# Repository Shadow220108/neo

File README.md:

<h1 align="center">
<br>

<br>
Neo
<br>
</h1>

<h3 align="center">

A wireless 75% keyboard 

</h3>

<div align="center">
  
</div>

Neo is a 75% mechanical keyboard built around the Nordic nRF52840. It works over Bluetooth and over USB-C, runs on a LiPo battery that charges from the same USB-C port, and it has hotswap switches so you can change the switches without soldering anything. The PCB is a 4 layer board designed in KiCad and the case is designed in Fusion 360.

## Features

- 84 keys in a 75% ANSI layout, so you still get the F row and arrow keys
- Bluetooth 5 and USB-C from one chip (nRF52840), works with ZMK
- Kailh hotswap sockets for MX style switches
- Single cell LiPo with an MCP73831 charger, it charges while you use it
- Power switch that cuts the regulator but still lets the battery charge
- XC6220 regulator with only 8uA idle current so the battery lasts long
- Battery voltage reading so you can see the battery percentage
- 2.4GHz chip antenna with a keepout area on all 4 layers
- SWD header for flashing the bootloader
- 3 part case (bottom, plate, top frame) with a typing angle

## PCB

| Switches | MCU and antenna |
| --- | --- |
|  |  |

The board is 304.8 x 144.3 mm with 4 layers. Top and bottom have the signals and a ground fill, inner 1 is a solid ground plane and inner 2 has some power traces. The matrix is 6 rows and 16 columns with a 1N4148W diode on every key. There are 512 vias on it which is kinda crazy lol.

The USB-C has 5.1k resistors on CC1 and CC2 so C to C chargers work, a 500mA fuse and a USBLC6 ESD chip. When USB is plugged in the keyboard runs from USB and charges the battery, and when you unplug it an AO3401A switches over to the battery.

| USB-C | Charger |
| --- | --- |
|  |  |

## Case

The case has 3 parts, a bottom tray with a tilt, a switch plate and a red top frame with some vent lines on it just for the looks. The PCB screws in with 6 M2 holes. Each part is about 314 x 159 mm, so you need a big printer bed for it or you have to split the parts.

| Bottom | Plate |
| --- | --- |
|  |  |

## Renders

| Red | Orange |
| --- | --- |
|  |  |

## BOM

|Component   |Description                                                               |Qty|Unit price ($)|Total ($)|Source       |
|------------|--------------------------------------------------------------------------|---|--------------|---------|-------------|
|PCBA        |JLCPCB 4 layer PCB, assembled                                             |1  |73.40         |73.40    |JLCPCB       |
|Switches    |Gateron G Pro 3.0, pack of 90                                             |1  |18.45         |18.45    |Kinetic Labs |
|Keycaps     |Keychron double shot PBT Cherry profile full set (218 keys, fits 75% ANSI)|1  |39.99         |39.99    |Keychron     |
|Stabilizers |Durock V3 screw-in set (4x 2u, 1x 6.25u)                                  |1  |13.99         |13.99    |Divinikey    |
|LiPo battery|3.7V 2000mAh, JST-PH                                                      |1  |12.50         |12.50    |Adafruit 2011|
|Total       |                                                                          |   |              |158.33   |             |

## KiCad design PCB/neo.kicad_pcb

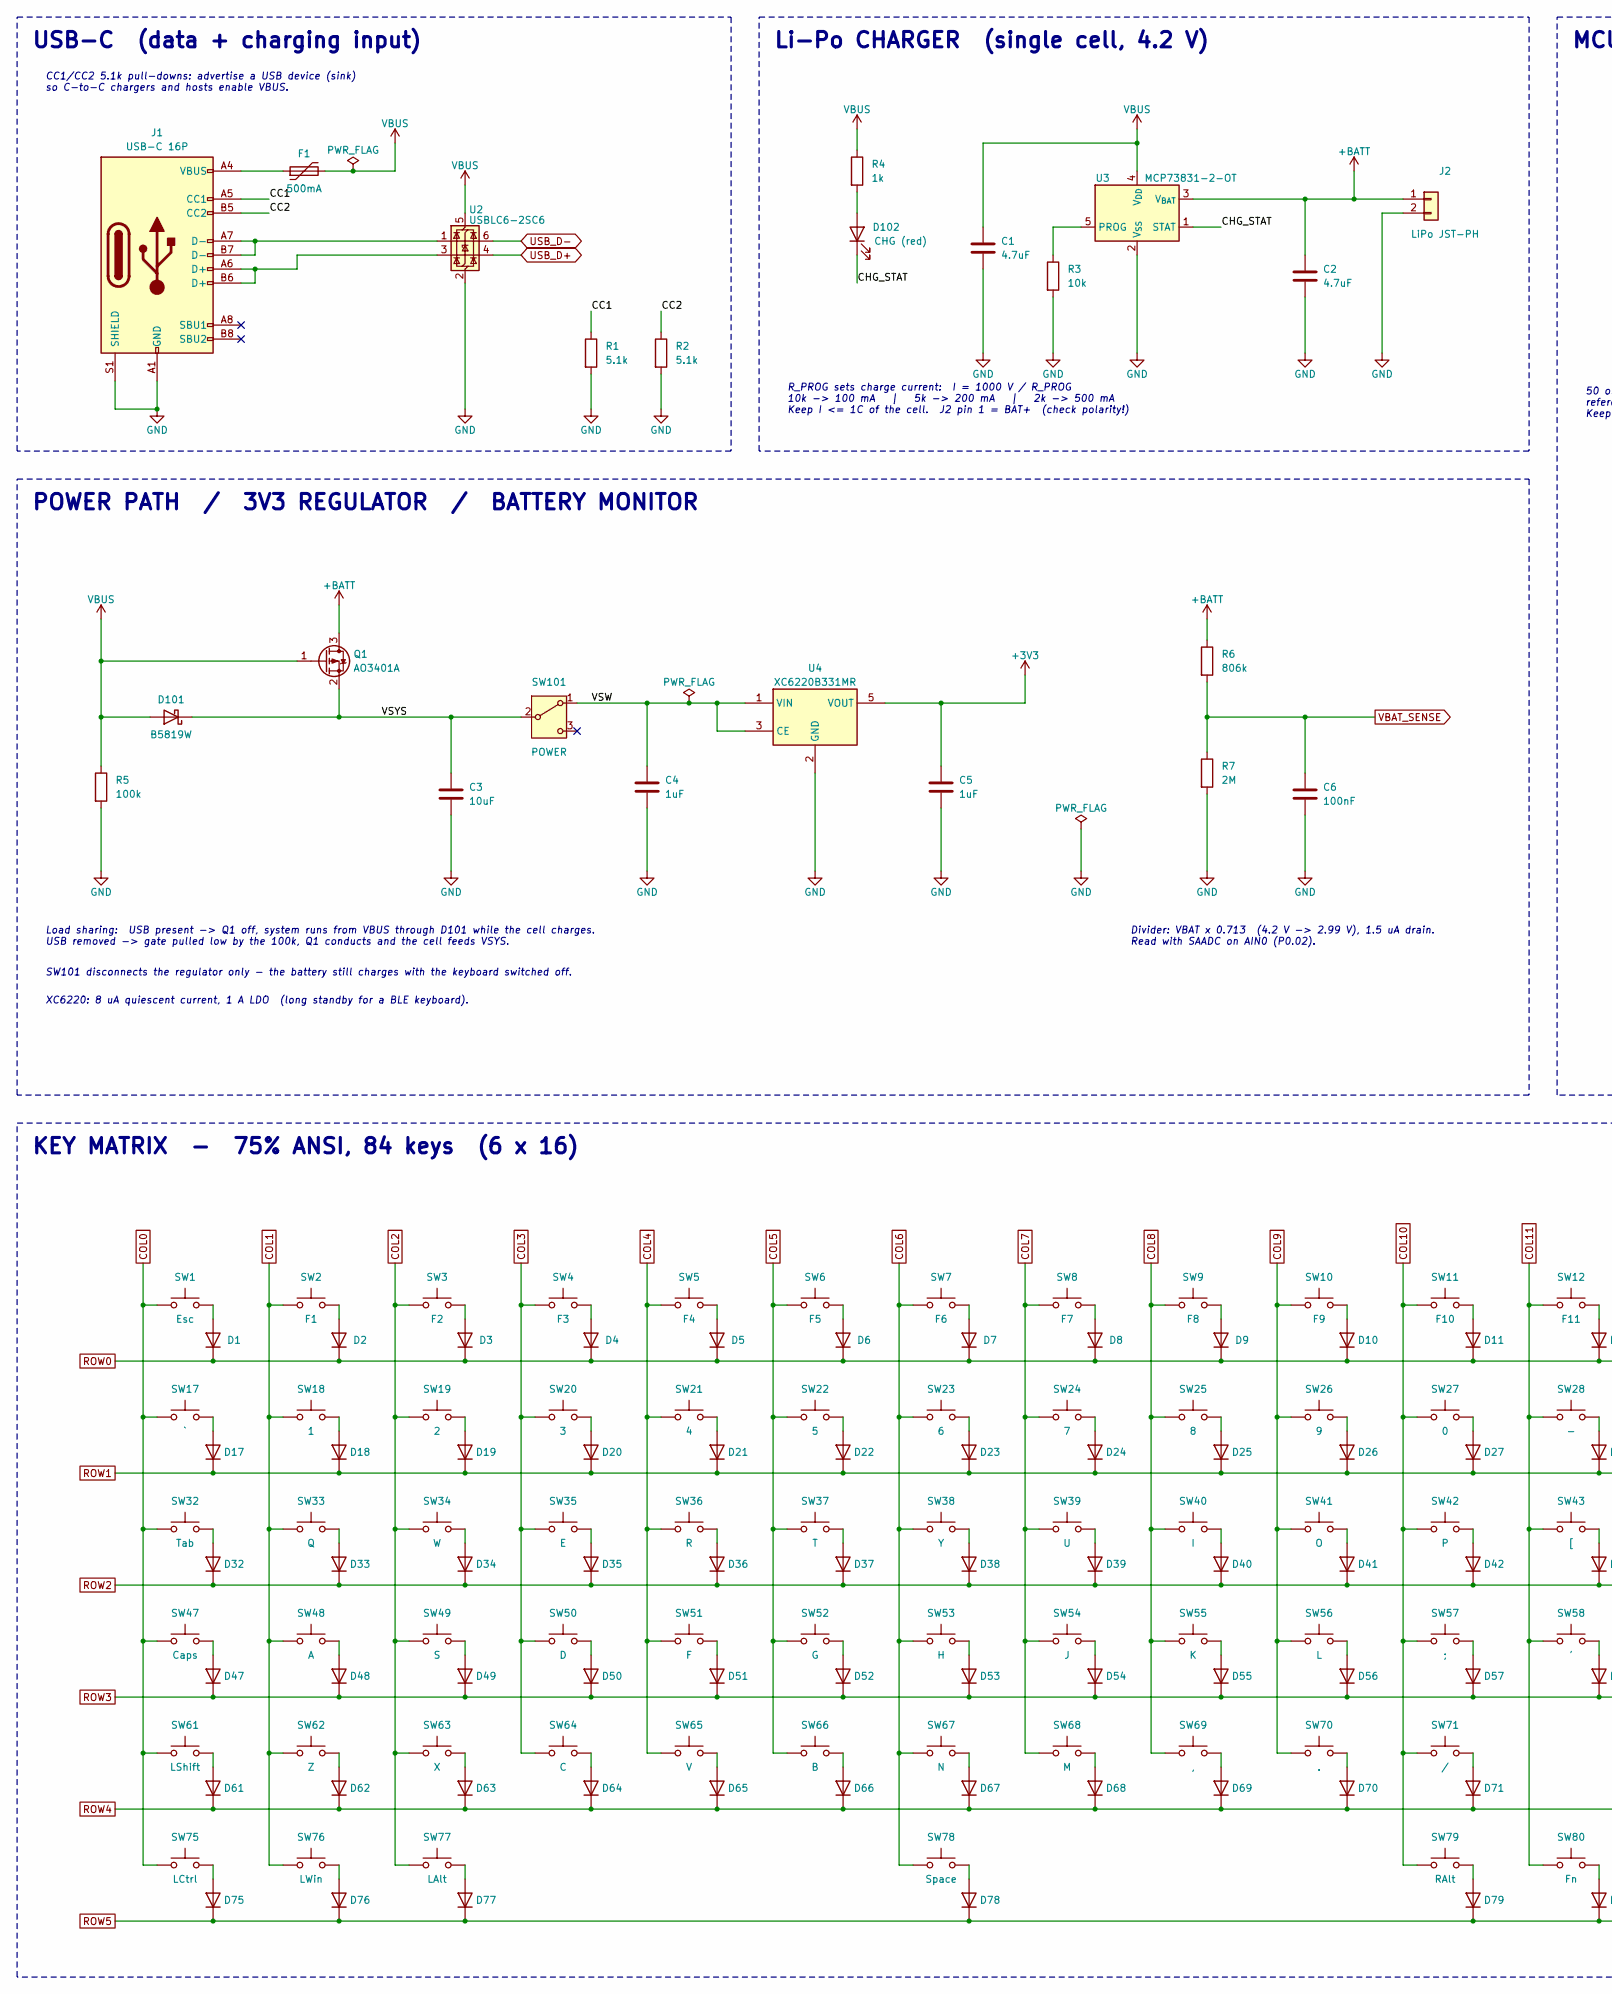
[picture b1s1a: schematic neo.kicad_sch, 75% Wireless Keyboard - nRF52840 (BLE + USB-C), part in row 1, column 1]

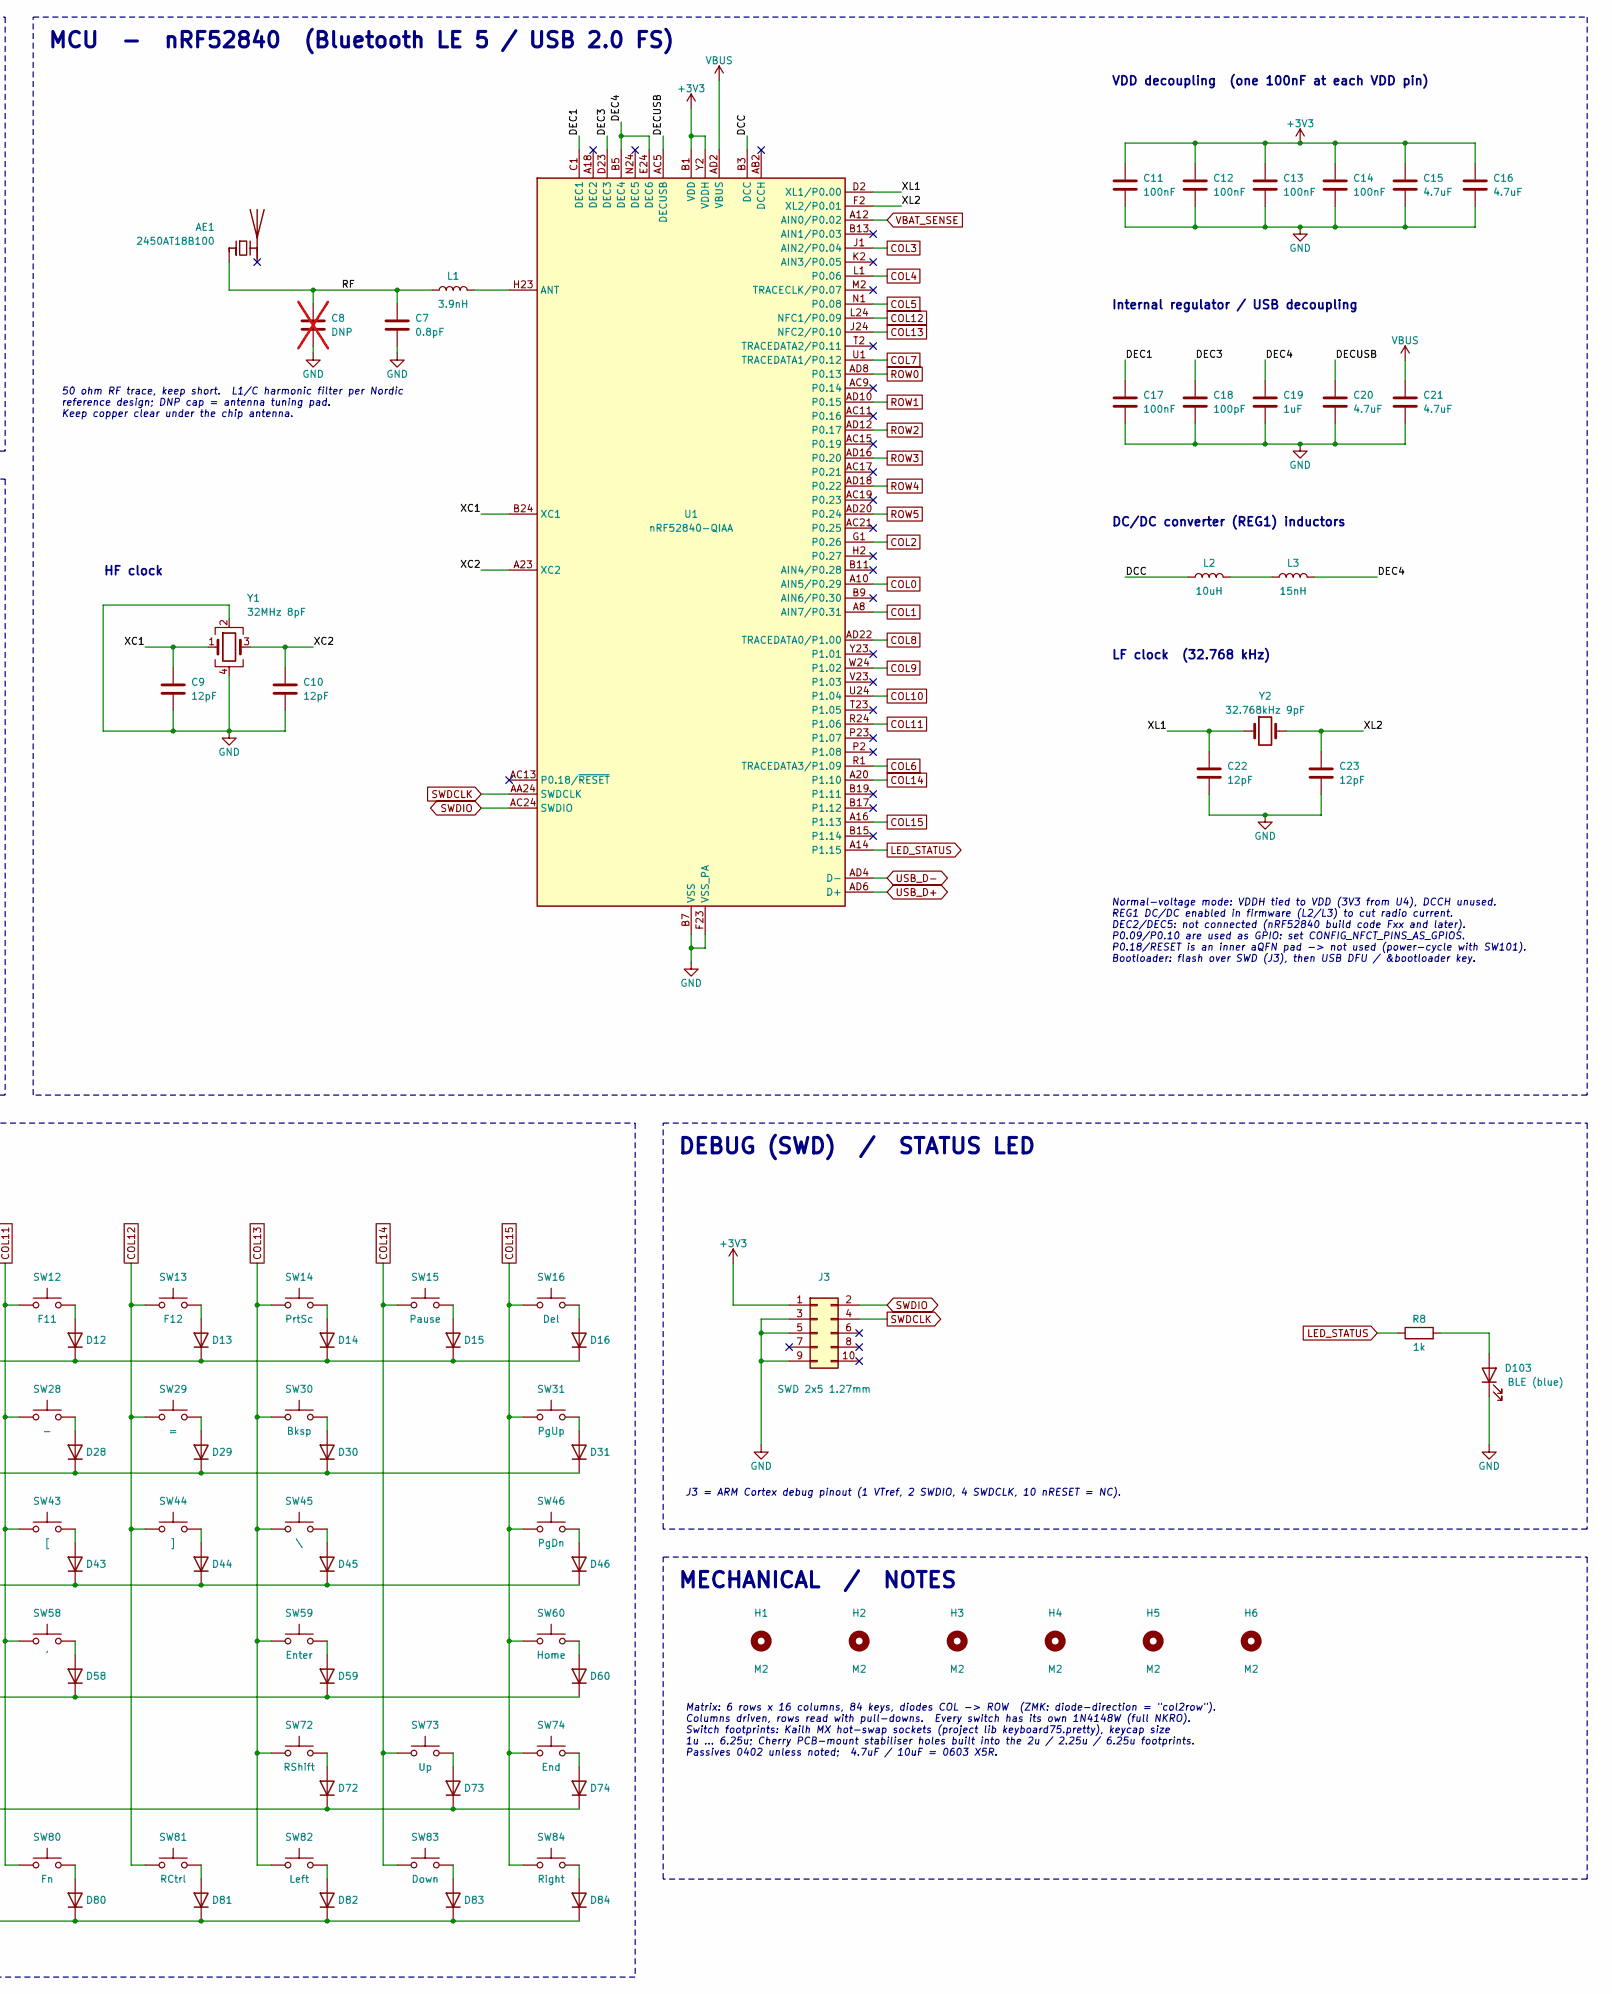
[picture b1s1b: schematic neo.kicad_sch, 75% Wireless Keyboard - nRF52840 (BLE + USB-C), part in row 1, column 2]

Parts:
AE1: 2450AT18B100; Johanson_2450AT18x100
C1, C2, C15, C16, C20, C21: 4.7uF; C_0603_1608Metric
C3: 10uF; C_0603_1608Metric
C4, C5, C19: 1uF; C_0402_1005Metric
C6, C11, C12, C13, C14, C17: 100nF; C_0402_1005Metric
C7: 0.8pF; C_0603_1608Metric
C8: DNP; C_0603_1608Metric; not fitted
C9, C10, C22, C23: 12pF; C_0402_1005Metric
C18: 100pF; C_0402_1005Metric
D1, D2, D3, D4, D5, D6, D7, D8, D9, D10, D11, D12, D13, D14, D15, D16, D17, D18, D19, D20, D21, D22, D23, D24, D25, D26, D27, D28, D29, D30, D31, D32, D33, D34, D35, D36, D37, D38, D39, D40, D41, D42, D43, D44, D45, D46, D47, D48, D49, D50, D51, D52, D53, D54, D55, D56, D57, D58, D59, D60, D61, D62, D63, D64, D65, D66, D67, D68, D69, D70, D71, D72, D73, D74, D75, D76, D77, D78, D79, D80, D81, D82, D83, D84: 1N4148W; D_SOD-123
D101: B5819W; D_SOD-123
D102: CHG (red); LED_0603_1608Metric
D103: BLE (blue); LED_0603_1608Metric
F1: 500mA; Fuse_0805_2012Metric
H1, H2, H3, H4, H5, H6: M2; MountingHole_2.2mm_M2
J1: USB-C 16P; USB_C_Receptacle_HRO_TYPE-C-31-M-12
J2: LiPo JST-PH; JST_PH_S2B-PH-K_1x02_P2.00mm_Horizontal
J3: SWD 2x5 1.27mm; PinHeader_2x05_P1.27mm_Vertical_SMD
L1: 3.9nH; L_0402_1005Metric
L2: 10uH; L_0603_1608Metric
L3: 15nH; L_0402_1005Metric
Q1: AO3401A; SOT-23
R1, R2: 5.1k; R_0402_1005Metric
R3: 10k; R_0402_1005Metric
R4, R8: 1k; R_0402_1005Metric
R5: 100k; R_0402_1005Metric
R6: 806k; R_0402_1005Metric
R7: 2M; R_0402_1005Metric
SW1: Esc; SW_Kailh_Hotswap_MX_1.00u
SW2: F1; SW_Kailh_Hotswap_MX_1.00u
SW3: F2; SW_Kailh_Hotswap_MX_1.00u
SW4: F3; SW_Kailh_Hotswap_MX_1.00u
SW5: F4; SW_Kailh_Hotswap_MX_1.00u
SW6: F5; SW_Kailh_Hotswap_MX_1.00u
SW7: F6; SW_Kailh_Hotswap_MX_1.00u
SW8: F7; SW_Kailh_Hotswap_MX_1.00u
SW9: F8; SW_Kailh_Hotswap_MX_1.00u
SW10: F9; SW_Kailh_Hotswap_MX_1.00u
SW11: F10; SW_Kailh_Hotswap_MX_1.00u
SW12: F11; SW_Kailh_Hotswap_MX_1.00u
SW13: F12; SW_Kailh_Hotswap_MX_1.00u
SW14: PrtSc; SW_Kailh_Hotswap_MX_1.00u
SW15: Pause; SW_Kailh_Hotswap_MX_1.00u
SW16: Del; SW_Kailh_Hotswap_MX_1.00u
SW17: `; SW_Kailh_Hotswap_MX_1.00u
SW18: 1; SW_Kailh_Hotswap_MX_1.00u
SW19: 2; SW_Kailh_Hotswap_MX_1.00u
SW20: 3; SW_Kailh_Hotswap_MX_1.00u
SW21: 4; SW_Kailh_Hotswap_MX_1.00u
SW22: 5; SW_Kailh_Hotswap_MX_1.00u
SW23: 6; SW_Kailh_Hotswap_MX_1.00u
SW24: 7; SW_Kailh_Hotswap_MX_1.00u
SW25: 8; SW_Kailh_Hotswap_MX_1.00u
SW26: 9; SW_Kailh_Hotswap_MX_1.00u
SW27: 0; SW_Kailh_Hotswap_MX_1.00u
SW28: -; SW_Kailh_Hotswap_MX_1.00u
SW29: =; SW_Kailh_Hotswap_MX_1.00u
SW30: Bksp; SW_Kailh_Hotswap_MX_2.00u
SW31: PgUp; SW_Kailh_Hotswap_MX_1.00u
SW32: Tab; SW_Kailh_Hotswap_MX_1.50u
SW33: Q; SW_Kailh_Hotswap_MX_1.00u
SW34: W; SW_Kailh_Hotswap_MX_1.00u
SW35: E; SW_Kailh_Hotswap_MX_1.00u
SW36: R; SW_Kailh_Hotswap_MX_1.00u
SW37: T; SW_Kailh_Hotswap_MX_1.00u
SW38: Y; SW_Kailh_Hotswap_MX_1.00u
SW39: U; SW_Kailh_Hotswap_MX_1.00u
SW40: I; SW_Kailh_Hotswap_MX_1.00u
SW41: O; SW_Kailh_Hotswap_MX_1.00u
SW42: P; SW_Kailh_Hotswap_MX_1.00u
SW43: [; SW_Kailh_Hotswap_MX_1.00u
SW44: ]; SW_Kailh_Hotswap_MX_1.00u
SW45: \; SW_Kailh_Hotswap_MX_1.50u
SW46: PgDn; SW_Kailh_Hotswap_MX_1.00u
SW47: Caps; SW_Kailh_Hotswap_MX_1.75u
SW48: A; SW_Kailh_Hotswap_MX_1.00u
SW49: S; SW_Kailh_Hotswap_MX_1.00u
SW50: D; SW_Kailh_Hotswap_MX_1.00u
SW51: F; SW_Kailh_Hotswap_MX_1.00u
SW52: G; SW_Kailh_Hotswap_MX_1.00u
SW53: H; SW_Kailh_Hotswap_MX_1.00u
SW54: J; SW_Kailh_Hotswap_MX_1.00u
SW55: K; SW_Kailh_Hotswap_MX_1.00u
SW56: L; SW_Kailh_Hotswap_MX_1.00u
SW57: ;; SW_Kailh_Hotswap_MX_1.00u
SW58: '; SW_Kailh_Hotswap_MX_1.00u
SW59: Enter; SW_Kailh_Hotswap_MX_2.25u
SW60: Home; SW_Kailh_Hotswap_MX_1.00u
SW61: LShift; SW_Kailh_Hotswap_MX_2.25u
SW62: Z; SW_Kailh_Hotswap_MX_1.00u
SW63: X; SW_Kailh_Hotswap_MX_1.00u
SW64: C; SW_Kailh_Hotswap_MX_1.00u
SW65: V; SW_Kailh_Hotswap_MX_1.00u
SW66: B; SW_Kailh_Hotswap_MX_1.00u
SW67: N; SW_Kailh_Hotswap_MX_1.00u
SW68: M; SW_Kailh_Hotswap_MX_1.00u
SW69: ,; SW_Kailh_Hotswap_MX_1.00u
SW70: .; SW_Kailh_Hotswap_MX_1.00u
SW71: /; SW_Kailh_Hotswap_MX_1.00u
SW72: RShift; SW_Kailh_Hotswap_MX_1.75u
SW73: Up; SW_Kailh_Hotswap_MX_1.00u
SW74: End; SW_Kailh_Hotswap_MX_1.00u
SW75: LCtrl; SW_Kailh_Hotswap_MX_1.25u
SW76: LWin; SW_Kailh_Hotswap_MX_1.25u
SW77: LAlt; SW_Kailh_Hotswap_MX_1.25u
SW78: Space; SW_Kailh_Hotswap_MX_6.25u
SW79: RAlt; SW_Kailh_Hotswap_MX_1.00u
SW80: Fn; SW_Kailh_Hotswap_MX_1.00u
SW81: RCtrl; SW_Kailh_Hotswap_MX_1.00u
SW82: Left; SW_Kailh_Hotswap_MX_1.00u
SW83: Down; SW_Kailh_Hotswap_MX_1.00u
SW84: Right; SW_Kailh_Hotswap_MX_1.00u
SW101: POWER; SW_SPDT_PCM12
U1: nRF52840-QIAA; Nordic_AQFN-73-1EP_7x7mm_P0.5mm
U2: USBLC6-2SC6; SOT-23-6
U3: MCP73831-2-OT; SOT-23-5
U4: XC6220B331MR; SOT-23-5
Y1: 32MHz 8pF; Crystal_SMD_2016-4Pin_2.0x1.6mm
Y2: 32.768kHz 9pF; Crystal_SMD_3215-2Pin_3.2x1.5mm

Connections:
+3V3: C5.1, C11.1, C12.1, C13.1, C14.1, C15.1, C16.1, J3.1, U1.A22 (VDD), U1.AD14 (VDD), U1.AD23 (VDD), U1.B1 (VDD), U1.W1 (VDD), U1.Y2 (VDDH), U4.5 (VOUT)
+BATT: C2.1, J2.1, Q1.3 (D), R6.1, U3.3 (V_{BAT})
CC1: J1.A5 (CC1), R1.1
CC2: J1.B5 (CC2), R2.1
CHG_STAT: D102.1 (K), U3.1 (STAT)
COL0: SW1.1, SW17.1, SW32.1, SW47.1, SW61.1, SW75.1, U1.A10 (AIN5/P0.29)
COL1: SW2.1, SW18.1, SW33.1, SW48.1, SW62.1, SW76.1, U1.A8 (AIN7/P0.31)
COL2: SW3.1, SW19.1, SW34.1, SW49.1, SW63.1, SW77.1, U1.G1 (P0.26)
COL3: SW4.1, SW20.1, SW35.1, SW50.1, SW64.1, U1.J1 (AIN2/P0.04)
COL4: SW5.1, SW21.1, SW36.1, SW51.1, SW65.1, U1.L1 (P0.06)
COL5: SW6.1, SW22.1, SW37.1, SW52.1, SW66.1, U1.N1 (P0.08)
COL6: SW7.1, SW23.1, SW38.1, SW53.1, SW67.1, SW78.1, U1.R1 (TRACEDATA3/P1.09)
COL7: SW8.1, SW24.1, SW39.1, SW54.1, SW68.1, U1.U1 (TRACEDATA1/P0.12)
COL8: SW9.1, SW25.1, SW40.1, SW55.1, SW69.1, U1.AD22 (TRACEDATA0/P1.00)
COL9: SW10.1, SW26.1, SW41.1, SW56.1, SW70.1, U1.W24 (P1.02)
COL10: SW11.1, SW27.1, SW42.1, SW57.1, SW71.1, SW79.1, U1.U24 (P1.04)
COL11: SW12.1, SW28.1, SW43.1, SW58.1, SW80.1, U1.R24 (P1.06)
COL12: SW13.1, SW29.1, SW44.1, SW81.1, U1.L24 (NFC1/P0.09)
COL13: SW14.1, SW30.1, SW45.1, SW59.1, SW72.1, SW82.1, U1.J24 (NFC2/P0.10)
COL14: SW15.1, SW73.1, SW83.1, U1.A20 (P1.10)
COL15: SW16.1, SW31.1, SW46.1, SW60.1, SW74.1, SW84.1, U1.A16 (P1.13)
DCC: L2.1, U1.B3 (DCC)
DEC1: C17.1, U1.C1 (DEC1)
DEC3: C18.1, U1.D23 (DEC3)
DEC4: C19.1, L3.2, U1.B5 (DEC4), U1.E24 (DEC6)
DECUSB: C20.1, U1.AC5 (DECUSB)
GND: C1.2, C2.2, C3.2, C4.2, C5.2, C6.2, C7.2, C8.2, C9.2, C10.2, C11.2, C12.2, C13.2, C14.2, C15.2, C16.2, C17.2, C18.2, C19.2, C20.2, C21.2, C22.2, C23.2, D103.1 (K), J1.A1 (GND), J1.A12 (GND), J1.B1 (GND), J1.B12 (GND), J1.S1 (SHIELD), J2.2, J3.3, J3.5, J3.9, R1.2, R2.2, R3.2, R5.2, R7.2, U1.B7 (VSS), U1.EP (VSS), U1.F23 (VSS_PA), U2.2 (GND), U3.2 (V_{SS}), U4.2 (GND), Y1.2, Y1.4
LED_STATUS: R8.1, U1.A14 (P1.15)
unnamed: D1.2 (A), SW1.2
unnamed: D2.2 (A), SW2.2
unnamed: D3.2 (A), SW3.2
unnamed: D4.2 (A), SW4.2
unnamed: D5.2 (A), SW5.2
unnamed: D6.2 (A), SW6.2
unnamed: D7.2 (A), SW7.2
unnamed: D8.2 (A), SW8.2
unnamed: D9.2 (A), SW9.2
unnamed: D10.2 (A), SW10.2
unnamed: D11.2 (A), SW11.2
unnamed: D12.2 (A), SW12.2
unnamed: D13.2 (A), SW13.2
unnamed: D14.2 (A), SW14.2
unnamed: D15.2 (A), SW15.2
unnamed: D16.2 (A), SW16.2
unnamed: D17.2 (A), SW17.2
unnamed: D18.2 (A), SW18.2
unnamed: D19.2 (A), SW19.2
unnamed: D20.2 (A), SW20.2
unnamed: D21.2 (A), SW21.2
unnamed: D22.2 (A), SW22.2
unnamed: D23.2 (A), SW23.2
unnamed: D24.2 (A), SW24.2
unnamed: D25.2 (A), SW25.2
unnamed: D26.2 (A), SW26.2
unnamed: D27.2 (A), SW27.2
unnamed: D28.2 (A), SW28.2
unnamed: D29.2 (A), SW29.2
unnamed: D30.2 (A), SW30.2
unnamed: D31.2 (A), SW31.2
unnamed: D32.2 (A), SW32.2
unnamed: D33.2 (A), SW33.2
unnamed: D34.2 (A), SW34.2
unnamed: D35.2 (A), SW35.2
unnamed: D36.2 (A), SW36.2
unnamed: D37.2 (A), SW37.2
unnamed: D38.2 (A), SW38.2
unnamed: D39.2 (A), SW39.2
unnamed: D40.2 (A), SW40.2
unnamed: D41.2 (A), SW41.2
unnamed: D42.2 (A), SW42.2
unnamed: D43.2 (A), SW43.2
unnamed: D44.2 (A), SW44.2
unnamed: D45.2 (A), SW45.2
unnamed: D46.2 (A), SW46.2
unnamed: D47.2 (A), SW47.2
unnamed: D48.2 (A), SW48.2
unnamed: D49.2 (A), SW49.2
unnamed: D50.2 (A), SW50.2
unnamed: D51.2 (A), SW51.2
unnamed: D52.2 (A), SW52.2
unnamed: D53.2 (A), SW53.2
unnamed: D54.2 (A), SW54.2
unnamed: D55.2 (A), SW55.2
unnamed: D56.2 (A), SW56.2
unnamed: D57.2 (A), SW57.2
unnamed: D58.2 (A), SW58.2
unnamed: D59.2 (A), SW59.2
unnamed: D60.2 (A), SW60.2
unnamed: D61.2 (A), SW61.2
unnamed: D62.2 (A), SW62.2
unnamed: D63.2 (A), SW63.2
unnamed: D64.2 (A), SW64.2
unnamed: D65.2 (A), SW65.2
unnamed: D66.2 (A), SW66.2
unnamed: D67.2 (A), SW67.2
unnamed: D68.2 (A), SW68.2
unnamed: D69.2 (A), SW69.2
unnamed: D70.2 (A), SW70.2
unnamed: D71.2 (A), SW71.2
unnamed: D72.2 (A), SW72.2
unnamed: D73.2 (A), SW73.2
unnamed: D74.2 (A), SW74.2
unnamed: D75.2 (A), SW75.2
unnamed: D76.2 (A), SW76.2
unnamed: D77.2 (A), SW77.2
unnamed: D78.2 (A), SW78.2
unnamed: D79.2 (A), SW79.2
unnamed: D80.2 (A), SW80.2
unnamed: D81.2 (A), SW81.2
unnamed: D82.2 (A), SW82.2
unnamed: D83.2 (A), SW83.2
unnamed: D84.2 (A), SW84.2
unnamed: F1.1, J1.A4 (VBUS), J1.A9 (VBUS), J1.B4 (VBUS), J1.B9 (VBUS)
unnamed: L1.2, U1.H23 (ANT)
unnamed: L2.2, L3.1
unnamed: R3.1, U3.5 (PROG)
unnamed: D102.2 (A), R4.2
unnamed: D103.2 (A), R8.2
unnamed: J1.A7 (D-), J1.B7 (D-), U2.1 (I/O1)
unnamed: J1.A6 (D+), J1.B6 (D+), U2.3 (I/O2)
RF: AE1.1 (FEED), C7.1, C8.1, L1.1
ROW0: D1.1 (K), D2.1 (K), D3.1 (K), D4.1 (K), D5.1 (K), D6.1 (K), D7.1 (K), D8.1 (K), D9.1 (K), D10.1 (K), D11.1 (K), D12.1 (K), D13.1 (K), D14.1 (K), D15.1 (K), D16.1 (K), U1.AD8 (P0.13)
ROW1: D17.1 (K), D18.1 (K), D19.1 (K), D20.1 (K), D21.1 (K), D22.1 (K), D23.1 (K), D24.1 (K), D25.1 (K), D26.1 (K), D27.1 (K), D28.1 (K), D29.1 (K), D30.1 (K), D31.1 (K), U1.AD10 (P0.15)
ROW2: D32.1 (K), D33.1 (K), D34.1 (K), D35.1 (K), D36.1 (K), D37.1 (K), D38.1 (K), D39.1 (K), D40.1 (K), D41.1 (K), D42.1 (K), D43.1 (K), D44.1 (K), D45.1 (K), D46.1 (K), U1.AD12 (P0.17)
ROW3: D47.1 (K), D48.1 (K), D49.1 (K), D50.1 (K), D51.1 (K), D52.1 (K), D53.1 (K), D54.1 (K), D55.1 (K), D56.1 (K), D57.1 (K), D58.1 (K), D59.1 (K), D60.1 (K), U1.AD16 (P0.20)
ROW4: D61.1 (K), D62.1 (K), D63.1 (K), D64.1 (K), D65.1 (K), D66.1 (K), D67.1 (K), D68.1 (K), D69.1 (K), D70.1 (K), D71.1 (K), D72.1 (K), D73.1 (K), D74.1 (K), U1.AD18 (P0.22)
ROW5: D75.1 (K), D76.1 (K), D77.1 (K), D78.1 (K), D79.1 (K), D80.1 (K), D81.1 (K), D82.1 (K), D83.1 (K), D84.1 (K), U1.AD20 (P0.24)
SWDCLK: J3.4, U1.AA24 (SWDCLK)
SWDIO: J3.2, U1.AC24 (SWDIO)
USB_D+: U1.AD6 (D+), U2.4 (I/O2)
USB_D-: U1.AD4 (D-), U2.6 (I/O1)
VBAT_SENSE: C6.1, R6.2, R7.1, U1.A12 (AIN0/P0.02)
VBUS: C1.1, C21.1, D101.2 (A), F1.2, Q1.1 (G), R4.1, R5.1, U1.AD2 (VBUS), U2.5 (VBUS), U3.4 (V_{DD})
VSW: C4.1, SW101.1 (A), U4.1 (VIN), U4.3 (CE)
VSYS: C3.1, D101.1 (K), Q1.2 (S), SW101.2 (B)
XC1: C9.1, U1.B24 (XC1), Y1.1
XC2: C10.1, U1.A23 (XC2), Y1.3
XL1: C22.1, U1.D2 (XL1/P0.00), Y2.1
XL2: C23.1, U1.F2 (XL2/P0.01), Y2.2

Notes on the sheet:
USB-C (data + charging input)
CC1/CC2 5.1k pull-downs: advertise a USB device (sink) so C-to-C chargers and hosts enable VBUS.
Li-Po CHARGER (single cell, 4.2 V)
R_PROG sets charge current: I = 1000 V / R_PROG 10k -> 100 mA | 5k -> 200 mA | 2k -> 500 mA Keep I <= 1C of the cell. J2 pin 1 = BAT+ (check polarity!)
POWER PATH / 3V3 REGULATOR / BATTERY MONITOR
Load sharing: USB present -> Q1 off, system runs from VBUS through D101 while the cell charges. USB removed -> gate pulled low by the 100k, Q1 conducts and the cell feeds VSYS.
SW101 disconnects the regulator only - the battery still charges with the keyboard switched off.
XC6220: 8 uA quiescent current, 1 A LDO (long standby for a BLE keyboard).
Divider: VBAT x 0.713 (4.2 V -> 2.99 V), 1.5 uA drain. Read with SAADC on AIN0 (P0.02).
MCU - nRF52840 (Bluetooth LE 5 / USB 2.0 FS)
50 ohm RF trace, keep short. L1/C harmonic filter per Nordic reference design; DNP cap = antenna tuning pad. Keep copper clear under the chip antenna.
HF clock
VDD decoupling (one 100nF at each VDD pin)
Internal regulator / USB decoupling
DC/DC converter (REG1) inductors
LF clock (32.768 kHz)
Normal-voltage mode: VDDH tied to VDD (3V3 from U4), DCCH unused. REG1 DC/DC enabled in firmware (L2/L3) to cut radio current. DEC2/DEC5: not connected (nRF52840 build code Fxx and later). P0.09/P0.10 are used as GPIO: set CONFIG_NFCT_PINS_AS_GPIOS. P0.18/RESET is an inner aQFN pad -> not used (pow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
DEBUG (SWD) / STATUS LED
J3 = ARM Cortex debug pinout (1 VTref, 2 SWDIO, 4 SWDCLK, 10 nRESET = NC).
MECHANICAL / NOTES
Matrix: 6 rows x 16 columns, 84 keys, diodes COL -> ROW (ZMK: diode-direction = "col2row"). Columns driven, rows read with pull-downs. Every switch has its own 1N4148W (full NKRO). Switch footprints: Kailh MX hot-swap sockets (project lib keyboard75.pretty), keycap size 1u ... 6.25u; Cherry PCB-mou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
KEY MATRIX - 75% ANSI, 84 keys (6 x 16)

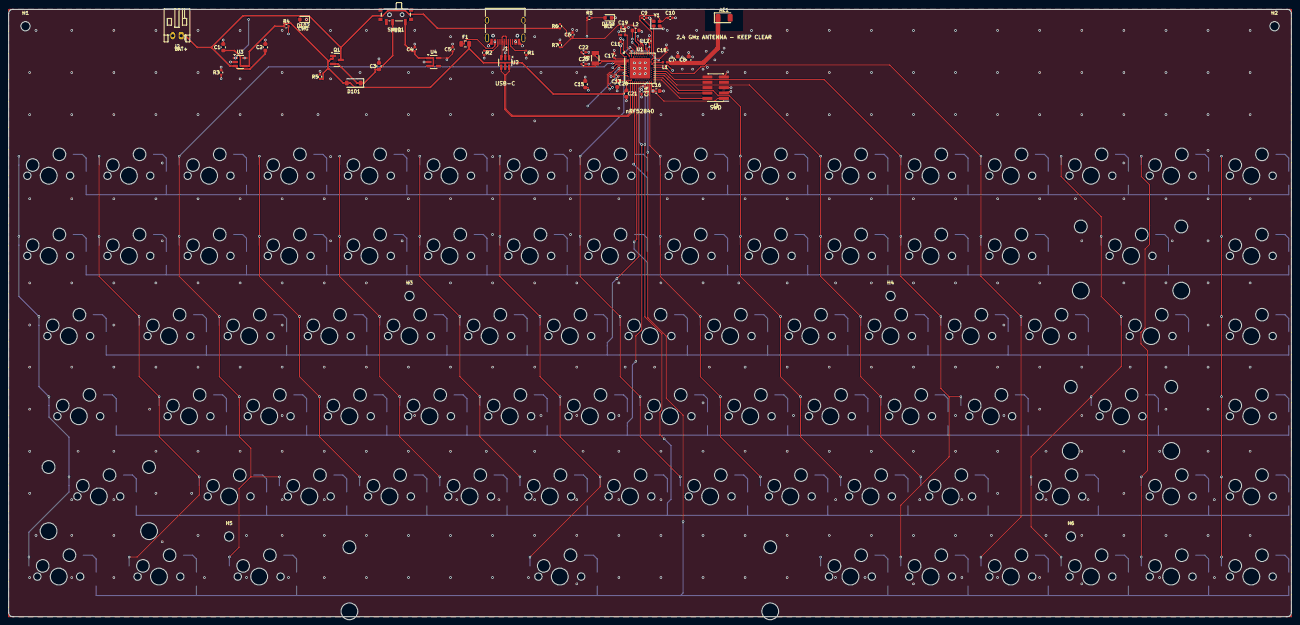
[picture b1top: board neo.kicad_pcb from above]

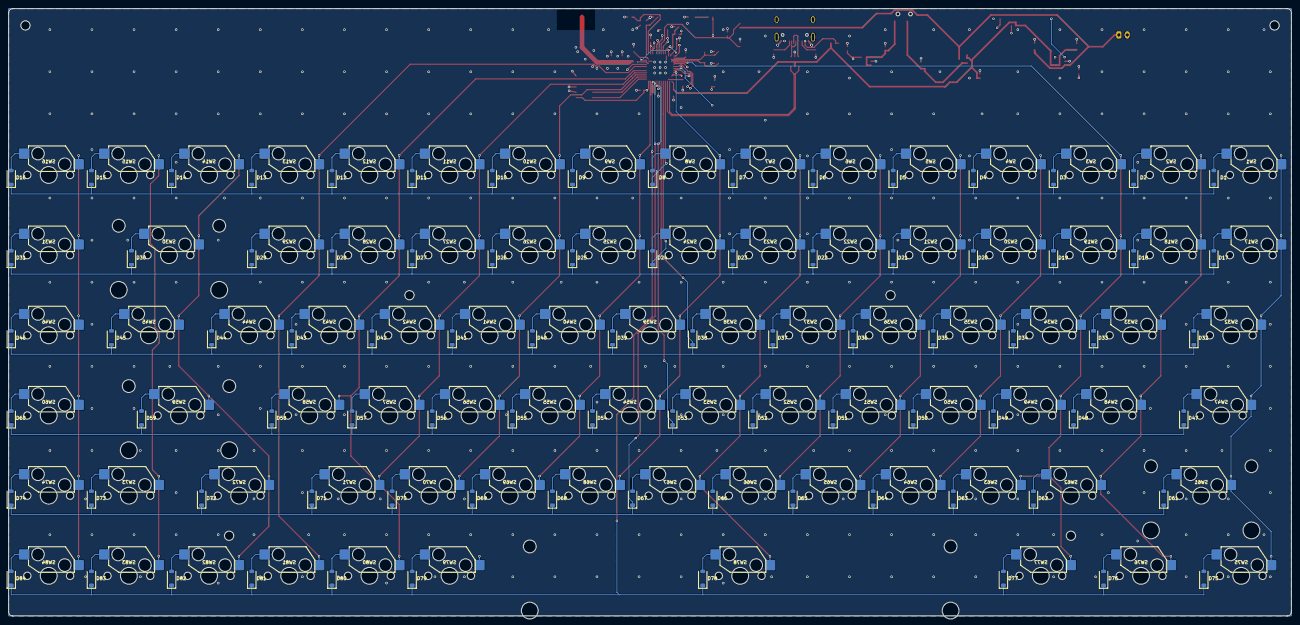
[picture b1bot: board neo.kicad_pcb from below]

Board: 4 copper layers, 304.8 x 144.3 mm, 224 parts (84 on the bottom side), 139 nets.
